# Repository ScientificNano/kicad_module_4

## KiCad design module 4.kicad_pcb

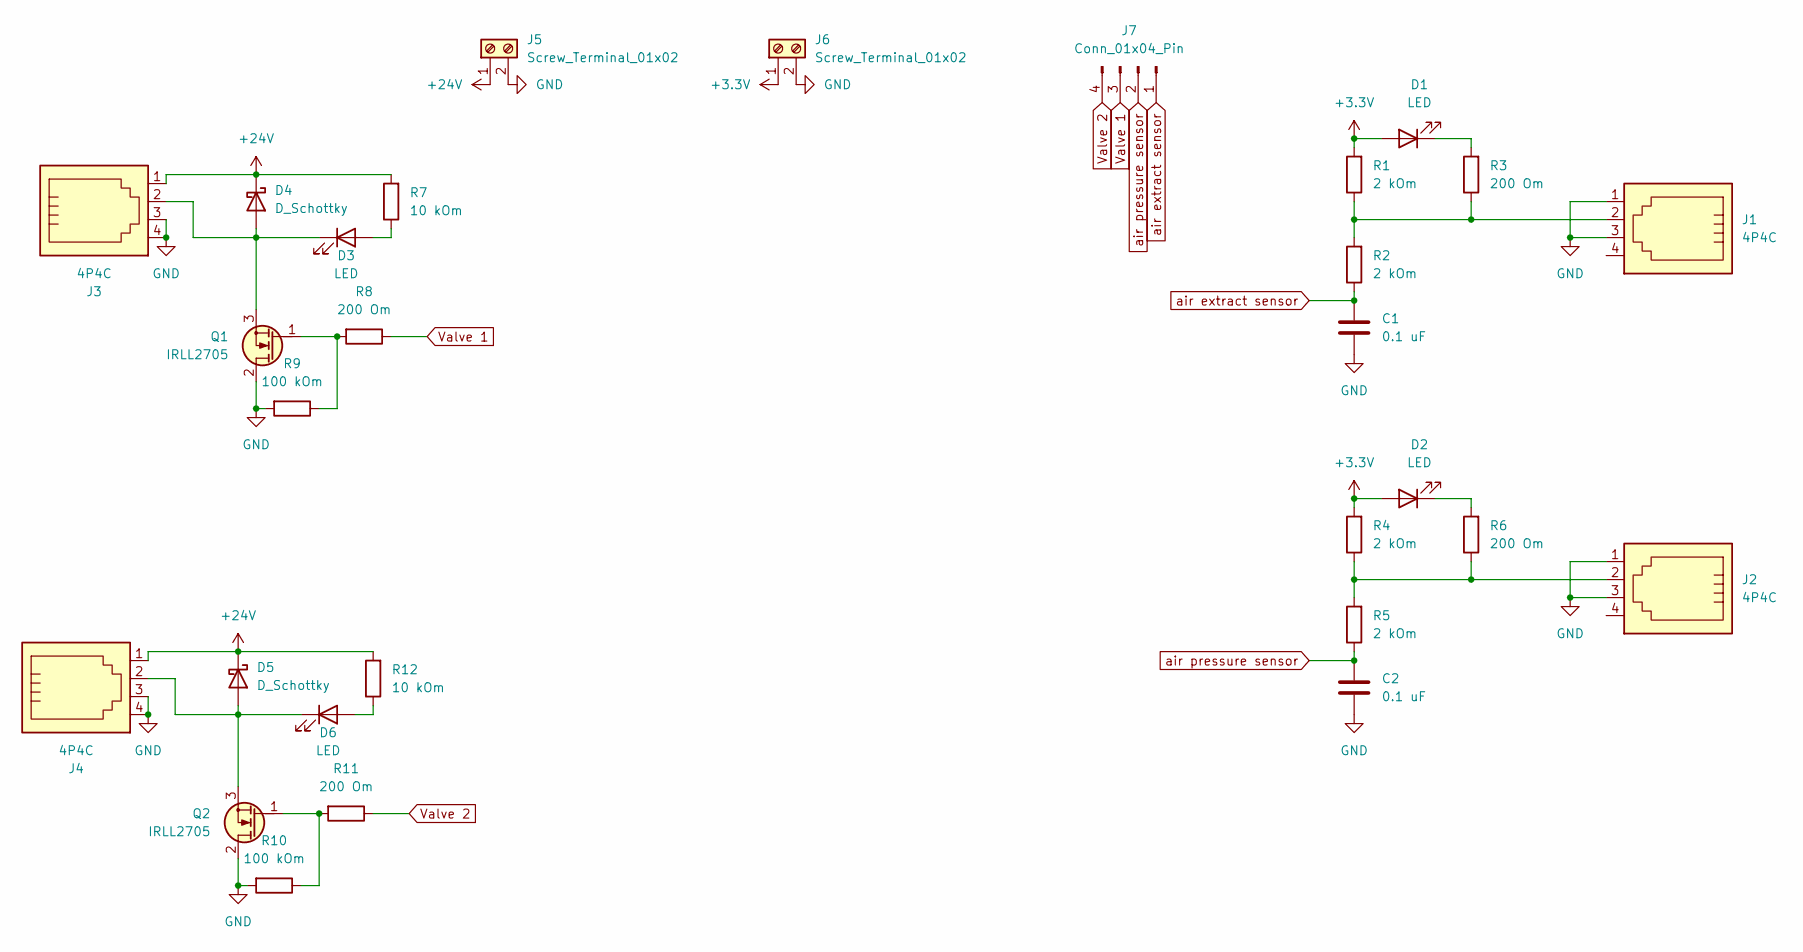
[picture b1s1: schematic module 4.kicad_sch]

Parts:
C1, C2: 0.1 uF; C_0805_2012Metric_Pad1.18x1.45mm_HandSolder
D1, D2, D3, D6: LED; LED_D5.0mm
D4, D5: D_Schottky; D_SMA
J1, J2, J3, J4: 4P4C; 4P4C_narrow
J5, J6: Screw_Terminal_01x02; TerminalBlock_bornier-2_P5.08mm
J7: Conn_01x04_Pin; PinHeader_1x04_P2.54mm_Vertical
Q1, Q2: IRLL2705; SOT-223-3_TabPin2
R1, R2, R4, R5: 2 kOm; R_0805_2012Metric_Pad1.20x1.40mm_HandSolder
R3, R6, R8, R11: 200 Om; R_0805_2012Metric_Pad1.20x1.40mm_HandSolder
R7, R12: 10 kOm; R_0805_2012Metric_Pad1.20x1.40mm_HandSolder
R9, R10: 100 kOm; R_0805_2012Metric_Pad1.20x1.40mm_HandSolder

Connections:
+3.3V: D1.2 (A), D2.2 (A), J6.1, R1.2, R4.2
+24V: D4.1 (K), D5.1 (K), J3.1, J4.1, J5.1, R7.2, R12.2
GND: C1.2, C2.2, J1.1, J1.3, J2.1, J2.3, J3.3, J3.4, J4.3, J4.4, J5.2, J6.2, Q1.2 (D), Q2.2 (D), R9.2, R10.2
unnamed: D1.1 (K), R3.2
unnamed: D2.1 (K), R6.2
unnamed: D3.2 (A), R7.1
unnamed: D3.1 (K), D4.2 (A), J3.2, Q1.3 (S)
unnamed: D5.2 (A), D6.1 (K), J4.2, Q2.3 (S)
unnamed: D6.2 (A), R12.1
unnamed: J1.2, R1.1, R2.2, R3.1
unnamed: J2.2, R4.1, R5.2, R6.1
unnamed: Q1.1 (G), R8.2, R9.1
unnamed: Q2.1 (G), R10.1, R11.2
Valve 1: J7.3, R8.1
Valve 2: J7.4, R11.1
air extract sensor: C1.1, J7.1, R2.1
air pressure sensor: C2.1, J7.2, R5.1

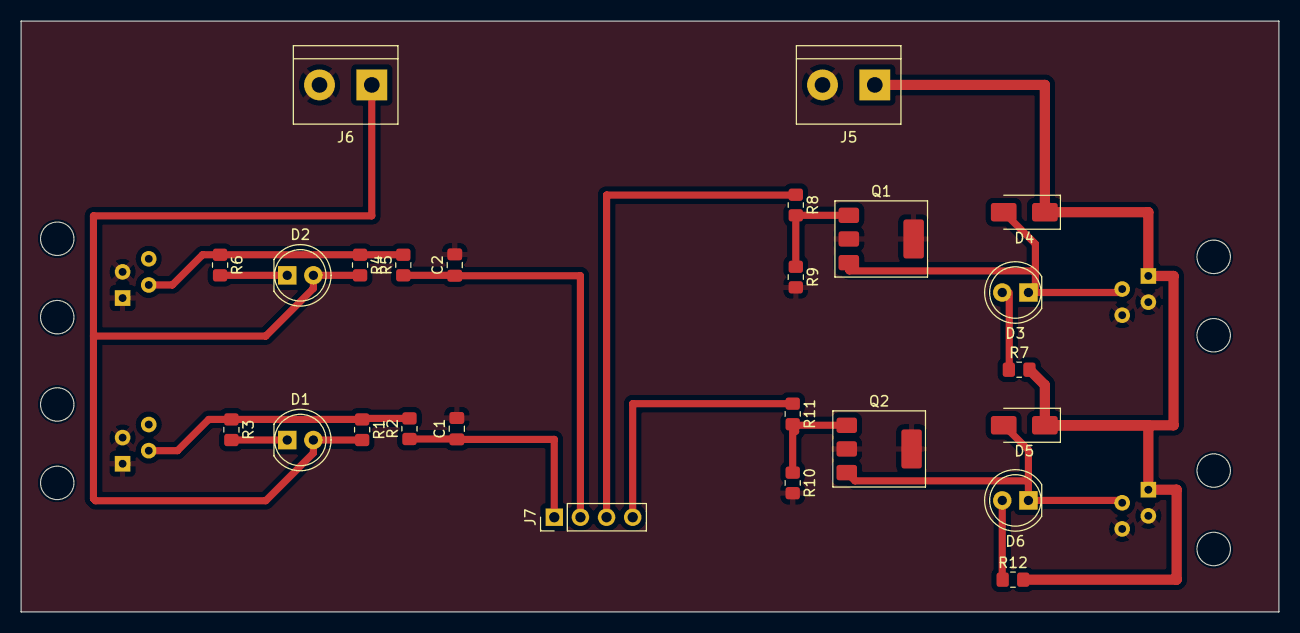
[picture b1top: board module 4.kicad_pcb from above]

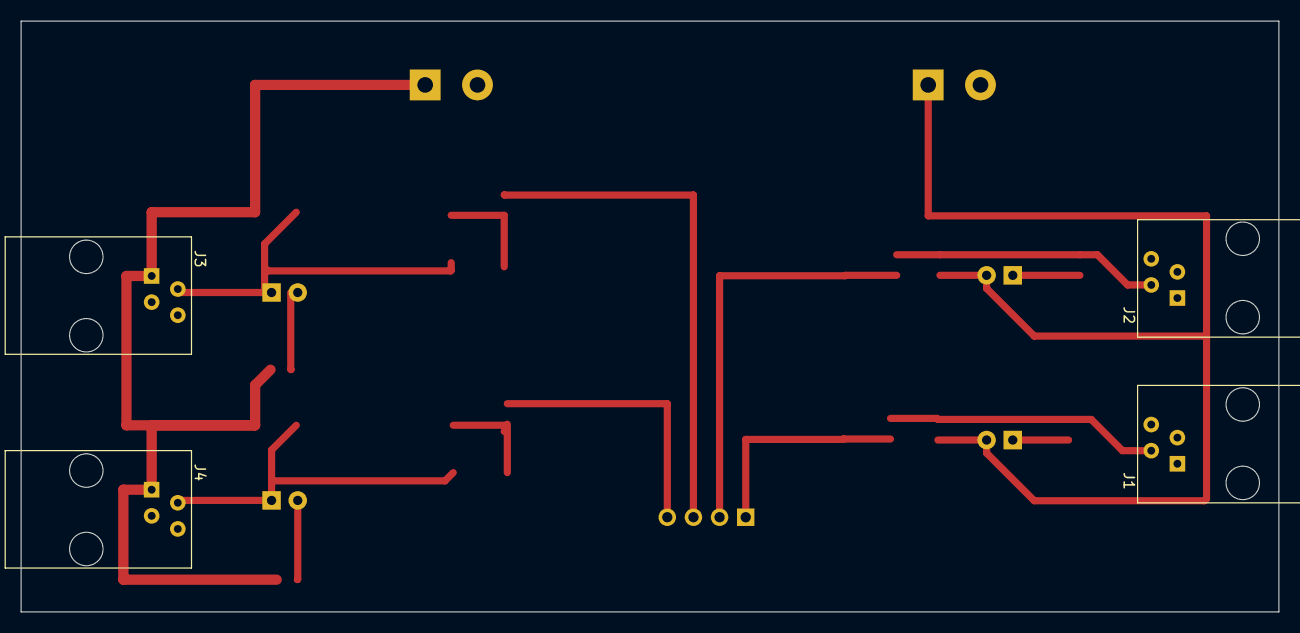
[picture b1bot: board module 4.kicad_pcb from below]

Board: 2 copper layers, 122.2 x 57.4 mm, 29 parts (4 on the bottom side), 17 nets.

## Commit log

2023-08-11 Add new module 4
